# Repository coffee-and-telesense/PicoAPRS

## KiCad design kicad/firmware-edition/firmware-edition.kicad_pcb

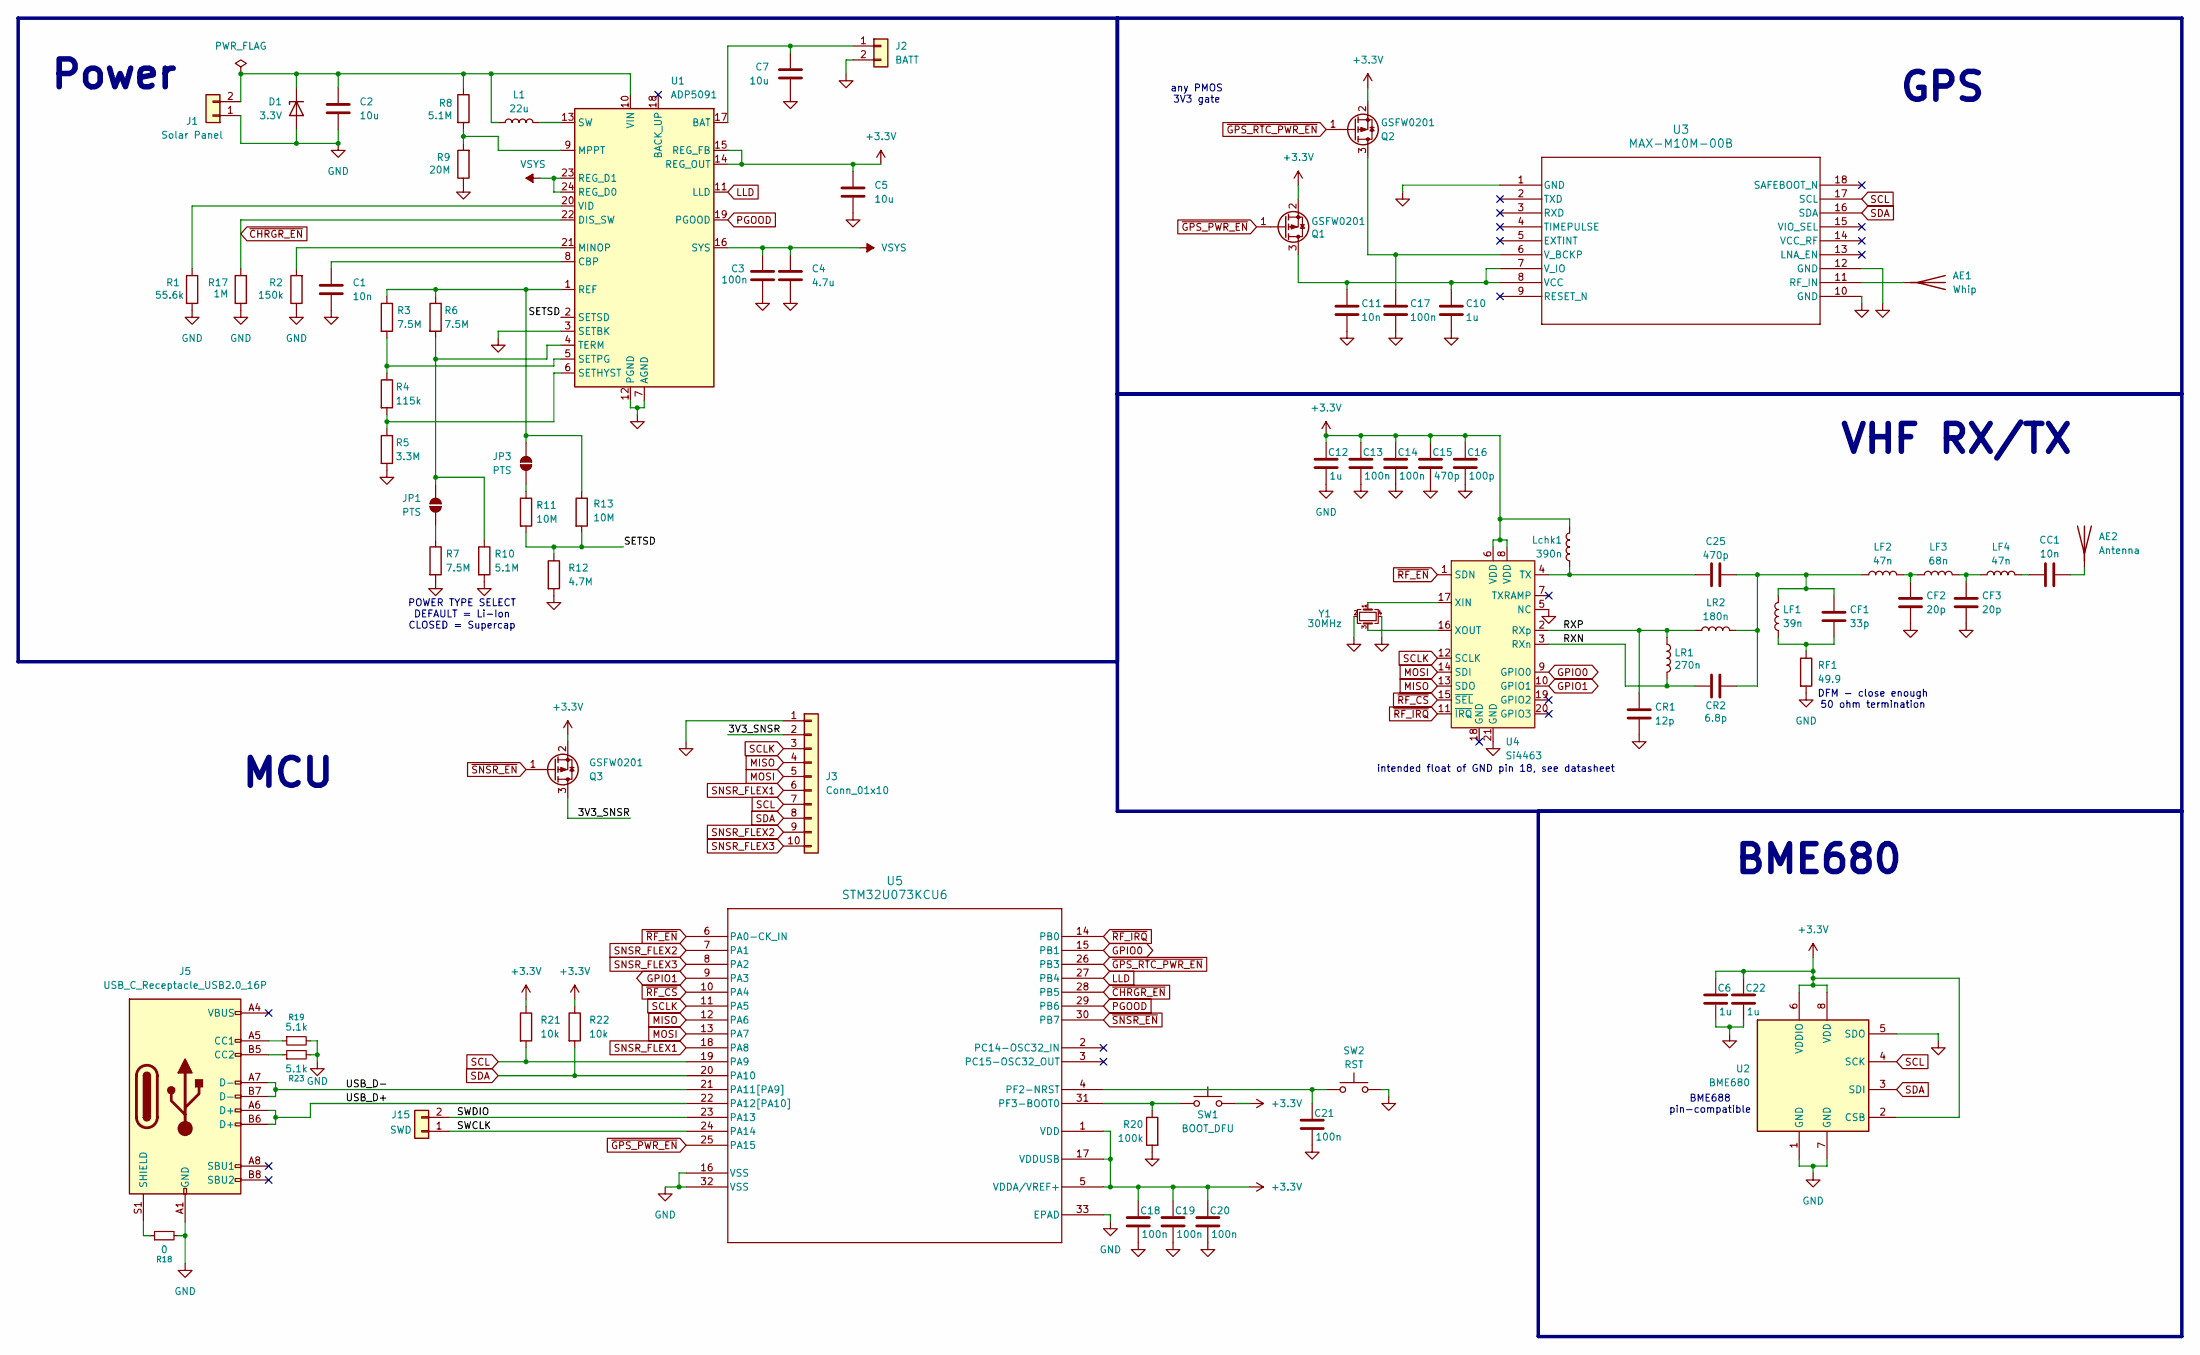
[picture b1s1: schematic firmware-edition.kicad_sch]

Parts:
AE1: Whip; SolderWirePad_1x01_SMD_1x2mm
AE2: Antenna; SolderWirePad_1x01_SMD_1x2mm
C1, C11: 10n; C_0402_1005Metric
C2, C5, C7: 10u; C_0402_1005Metric
C3, C13, C14, C17, C18, C19, C20, C21: 100n; C_0402_1005Metric
C4: 4.7u; C_0402_1005Metric
C6, C10, C12, C22: 1u; C_0402_1005Metric
C15, C25: 470p; C_0402_1005Metric
C16: 100p; C_0402_1005Metric
CC1: 10n; C_0402_1005Metric
CF1: 33p; C_0402_1005Metric
CF2, CF3: 20p; C_0402_1005Metric
CR1: 12p; C_0402_1005Metric
CR2: 6.8p; C_0402_1005Metric
D1: 3.3V; D_0402_1005Metric_Pad0.77x0.64mm_HandSolder
J1: Solar Panel; C_Disc_D3.0mm_W1.6mm_P2.50mm
J2: BATT; C_Disc_D3.0mm_W1.6mm_P2.50mm
J3: Conn_01x10; CON_513389873
J5: USB_C_Receptacle_USB2.0_16P; USB_C_Receptacle_Palconn_UTC16-G
J15: SWD; PinHeader_1x02_P2.54mm_Vertical
JP1, JP3: PTS; SolderJumper-2_P1.3mm_Open_TrianglePad1.0x1.5mm
L1: 22u; L_Vishay_IFSC-1515AH_4x4x1.8mm
LF1: 39n; L_0402_1005Metric
LF2, LF4: 47n; L_0402_1005Metric
LF3: 68n; L_0402_1005Metric
LR1: 270n; L_0402_1005Metric
LR2: 180n; L_0402_1005Metric
Lchk1: 390n; L_0402_1005Metric
Q1, Q2, Q3: GSFW0201; SOT-883
R1: 55.6k; R_0402_1005Metric
R2: 150k; R_0402_1005Metric
R3, R6, R7: 7.5M; R_0402_1005Metric
R4: 115k; R_0402_1005Metric
R5: 3.3M; R_0402_1005Metric
R8, R10: 5.1M; R_0402_1005Metric
R9: 20M; R_0402_1005Metric
R11, R13: 10M; R_0402_1005Metric
R12: 4.7M; R_0402_1005Metric
R17: 1M; R_0402_1005Metric
R18: 0; R_0402_1005Metric
R19, R23: 5.1k; R_0402_1005Metric
R20: 100k; R_0402_1005Metric
R21, R22: 10k; R_0402_1005Metric
RF1: 49.9; R_0402_1005Metric
SW1: BOOT_DFU; SW_Push_1TS009xxxx-xxxx-xxxx_6x6x5mm
SW2: RST; SW_Push_1TS009xxxx-xxxx-xxxx_6x6x5mm
U1: ADP5091; LFCSP-24-1EP_4x4mm_P0.5mm_EP2.3x2.3mm
U2: BME680; Bosch_LGA-8_3x3mm_P0.8mm_ClockwisePinNumbering
U3: MAX-M10M-00B; MOD18_MAX-M10M_UBL
U4: Si4463; QFN-20-1EP_4x4mm_P0.5mm_EP2.6x2.6mm
U5: STM32U073KCU6; UFQFPN-32_STM
Y1: 30MHz; Crystal_SMD_2520-4Pin_2.5x2.0mm

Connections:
+3.3V: C5.1, C6.1, C12.1, C13.1, C14.1, C15.1, C16.1, C18.1, C19.1, C20.1, C22.1, Lchk1.1, Q1.2 (S), Q2.2 (S), Q3.2 (S), R21.1, R22.1, SW1.2, U1.14 (REG_OUT), U1.15 (REG_FB), U2.2 (CSB), U2.6 (VDDIO), U2.8 (VDD), U4.6 (VDD), U4.8 (VDD), U5.1 (VDD), U5.5 (VDDA/VREF+), U5.17 (VDDUSB)
/3V3_SNSR: J3.2, Q3.3 (D)
/RXN: CR2.1, LR1.1, U4.3 (RXn)
/RXP: CR1.1, LR1.2, LR2.1, U4.2 (RXp)
/SETSD: R11.2, R12.1, R13.2, U1.2 (SETSD)
/SWCLK: J15.1, U5.24 (PA14)
/SWDIO: J15.2, U5.23 (PA13)
/USB_D+: J5.A6 (D+), J5.B6 (D+), U5.22 (PA12[PA10])
/USB_D-: J5.A7 (D-), J5.B7 (D-), U5.21 (PA11[PA9])
GND: C1.2, C2.2, C3.2, C4.2, C5.2, C6.2, C7.2, C10.2, C11.2, C12.2, C13.2, C14.2, C15.2, C16.2, C17.2, C18.2, C19.2, C20.2, C21.2, C22.2, CF2.2, CF3.2, CR1.2, D1.2 (A), J1.1, J2.2, J3.1, J5.A1 (GND), J5.A12 (GND), J5.B1 (GND), J5.B12 (GND), R1.2, R2.1, R5.2, R7.2, R9.1, R10.2, R12.2, R17.1, R18.2, R19.2, R20.2, R23.2, RF1.2, SW2.2, U1.3 (SETBK), U1.7 (AGND), U1.12 (PGND), U1.25 (AGND), U2.1 (GND), U2.5 (SDO), U2.7 (GND), U3.1 (GND), U3.10 (GND), U3.12 (GND), U4.5 (NC), U4.21 (GND), U5.16 (VSS), U5.32 (VSS), U5.33 (EPAD), Y1.2, Y1.4
GPIO0: U4.9 (GPIO0), U5.15 (PB1)
GPIO1: U4.10 (GPIO1), U5.9 (PA3)
LLD: U1.11 (LLD), U5.27 (PB4)
MISO: J3.4, U4.13 (SDO), U5.12 (PA6)
MOSI: J3.5, U4.14 (SDI), U5.13 (PA7)
unnamed: AE1.1 (A), U3.11 (RF_IN)
unnamed: AE2.1 (A), CC1.2
unnamed: C25.2, CF1.1, CR2.2, LF1.2, LF2.1, LR2.2
unnamed: CC1.1, LF4.2
unnamed: CF1.2, LF1.1, RF1.1
unnamed: CF2.1, LF2.2, LF3.1
unnamed: CF3.1, LF3.2, LF4.1
unnamed: C2.1, D1.1 (K), J1.2, L1.1, R8.1, U1.10 (VIN)
unnamed: C7.1, J2.1, U1.17 (BAT)
unnamed: J5.A5 (CC1), R19.1
unnamed: J5.B5 (CC2), R23.1
unnamed: J5.S1 (SHIELD), R18.1
unnamed: JP1.1 (A), R7.1
unnamed: JP1.2 (B), R6.2, R10.1, U1.4 (TERM)
unnamed: JP3.1 (A), R11.1
unnamed: JP3.2 (B), R3.1, R6.1, R13.1, U1.1 (REF)
unnamed: C10.1, C11.1, Q1.3 (D), U3.7 (V_IO), U3.8 (VCC)
unnamed: C17.1, Q2.3 (D), U3.6 (V_BCKP)
unnamed: C1.1, U1.8 (CBP)
unnamed: R2.2, U1.21 (MINOP)
unnamed: R8.2, R9.2, U1.9 (MPPT)
unnamed: R4.2, R5.1, U1.6 (SETHYST)
unnamed: R3.2, R4.1, U1.5 (SETPG)
unnamed: L1.2, U1.13 (SW)
unnamed: R1.1, U1.20 (VID)
unnamed: C25.1, Lchk1.2, U4.4 (TX)
unnamed: U4.17 (XIN), Y1.1
unnamed: U4.16 (XOUT), Y1.3
unnamed: C21.1, SW2.1, U5.4 (PF2-NRST)
unnamed: R20.1, SW1.1, U5.31 (PF3-BOOT0)
PGOOD: U1.19 (PGOOD), U5.29 (PB6)
SCL: J3.7, R21.2, U2.4 (SCK), U3.17 (SCL), U5.19 (PA9)
SCLK: J3.3, U4.12 (SCLK), U5.11 (PA5)
SDA: J3.8, R22.2, U2.3 (SDI), U3.16 (SDA), U5.20 (PA10)
SNSR_FLEX1: J3.6, U5.18 (PA8)
SNSR_FLEX2: J3.9, U5.7 (PA1)
SNSR_FLEX3: J3.10, U5.8 (PA2)
VSYS: C3.1, C4.1, U1.16 (SYS), U1.23 (REG_D1), U1.24 (REG_D0)
~CHRGR_EN: R17.2, U1.22 (DIS_SW), U5.28 (PB5)
~GPS_PWR_EN: Q1.1 (G), U5.25 (PA15)
~GPS_RTC_PWR_EN: Q2.1 (G), U5.26 (PB3)
~RF_CS: U4.15 (~SEL), U5.10 (PA4)
~RF_EN: U4.1 (SDN), U5.6 (PA0-CK_IN)
~RF_IRQ: U4.11 (~IRQ), U5.14 (PB0)
~SNSR_EN: Q3.1 (G), U5.30 (PB7)

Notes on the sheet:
intended float of GND pin 18, see datasheet
GPS
DFM - close enough 50 ohm termination
Power
MCU
BME688 pin-compatible
VHF RX/TX
BME680
any PMOS 3V3 gate
POWER TYPE SELECT DEFAULT = Li-Ion CLOSED = Supercap

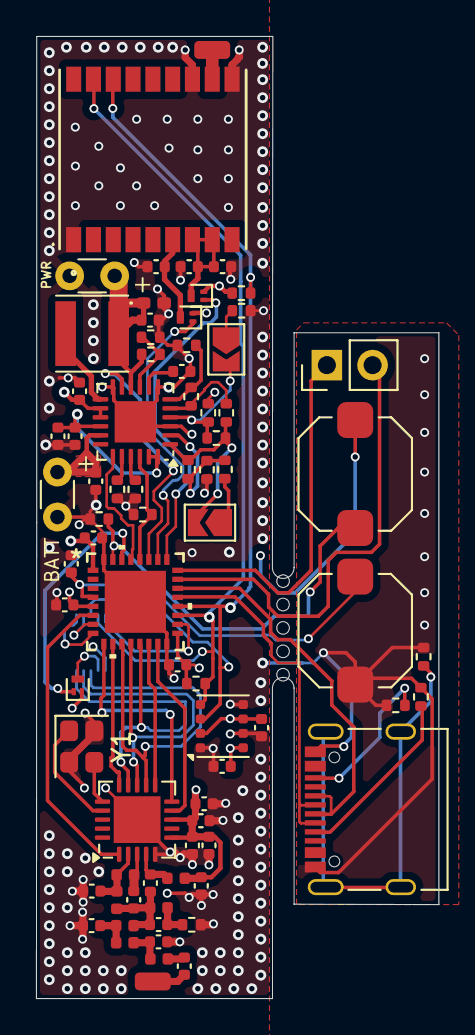
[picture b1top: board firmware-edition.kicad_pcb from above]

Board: 4 copper layers, 22.4 x 53.4 mm, 77 parts (1 on the bottom side), 60 nets.

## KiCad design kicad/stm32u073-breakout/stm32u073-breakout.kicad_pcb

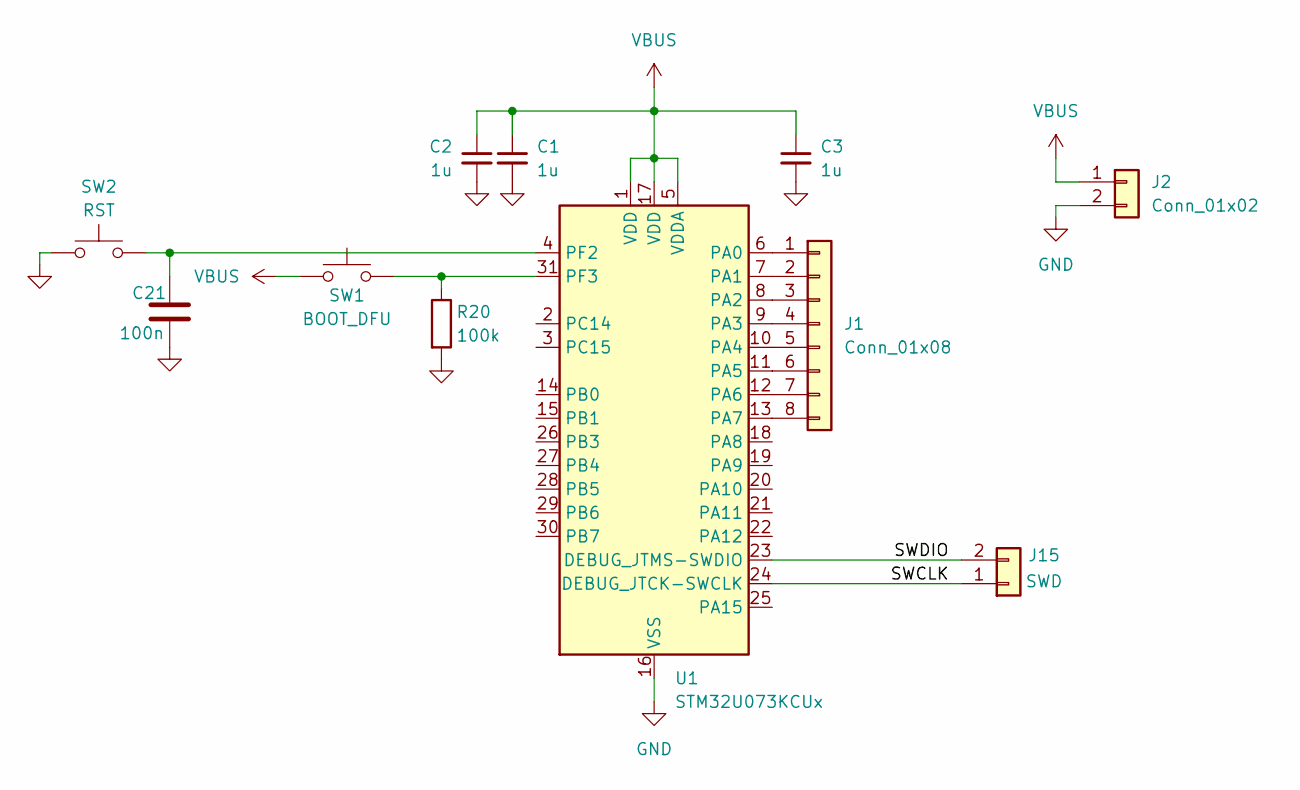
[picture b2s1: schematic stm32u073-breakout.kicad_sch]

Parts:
C1, C2, C3: 1u; C_0603_1608Metric
C21: 100n; C_0603_1608Metric
J1: Conn_01x08; PinHeader_1x08_P2.54mm_Vertical
J2: Conn_01x02; PinHeader_1x02_P2.54mm_Vertical
J15: SWD; PinHeader_1x02_P2.54mm_Vertical
R20: 100k; R_0603_1608Metric
SW1: BOOT_DFU; SW_SPST_B3S-1000
SW2: RST; SW_SPST_B3S-1000
U1: STM32U073KCUx; QFN-32-1EP_5x5mm_P0.5mm_EP3.45x3.45mm

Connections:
/SWCLK: J15.1, U1.24 (DEBUG_JTCK-SWCLK)
/SWDIO: J15.2, U1.23 (DEBUG_JTMS-SWDIO)
GND: C1.2, C2.2, C3.2, C21.2, J2.2, R20.2, SW2.2, U1.16 (VSS), U1.32 (VSS), U1.33 (VSS)
unnamed: J1.1, U1.6 (PA0)
unnamed: J1.2, U1.7 (PA1)
unnamed: J1.3, U1.8 (PA2)
unnamed: J1.4, U1.9 (PA3)
unnamed: J1.5, U1.10 (PA4)
unnamed: J1.6, U1.11 (PA5)
unnamed: J1.7, U1.12 (PA6)
unnamed: J1.8, U1.13 (PA7)
unnamed: C21.1, SW2.1, U1.4 (PF2)
unnamed: R20.1, SW1.1, U1.31 (PF3)
VBUS: C1.1, C2.1, C3.1, J2.1, SW1.2, U1.1 (VDD), U1.5 (VDDA), U1.17 (VDD)

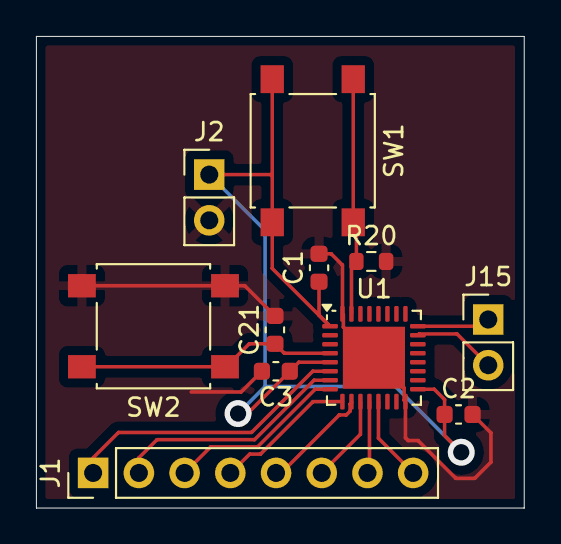
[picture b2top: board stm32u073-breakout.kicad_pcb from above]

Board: 2 copper layers, 27.1 x 26.2 mm, 11 parts (0 on the bottom side), 14 nets.

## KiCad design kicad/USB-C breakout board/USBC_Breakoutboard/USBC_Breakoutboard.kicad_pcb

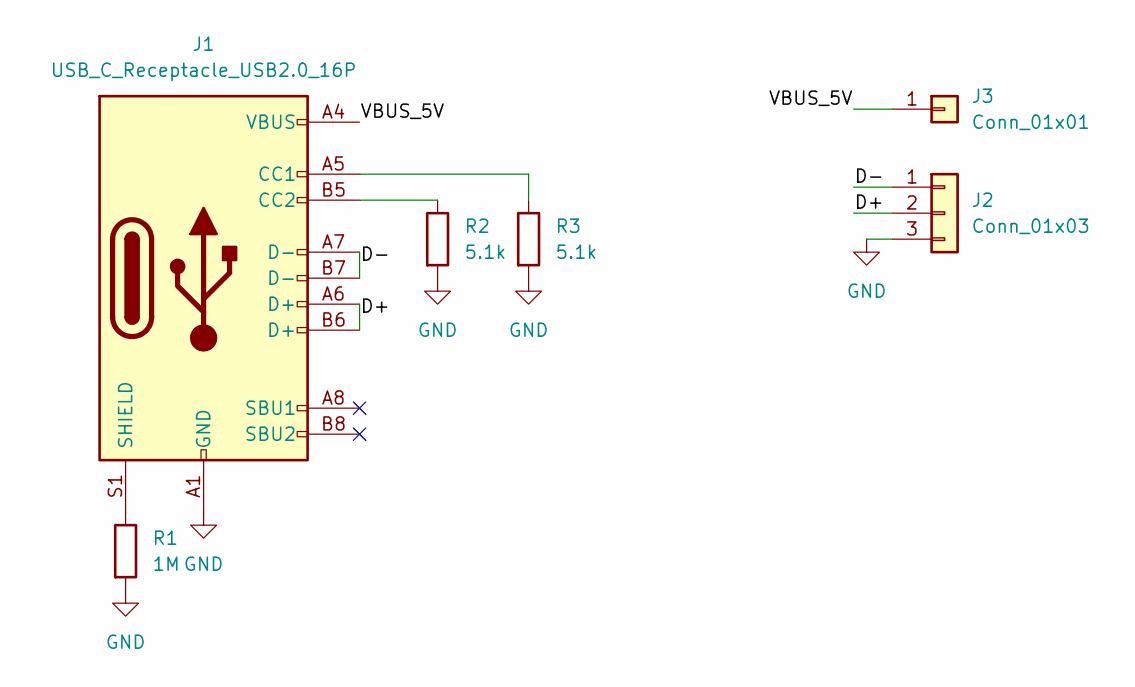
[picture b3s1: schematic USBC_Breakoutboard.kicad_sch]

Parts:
J1: USB_C_Receptacle_USB2.0_16P; USB_C_Receptacle_GCT_USB4105-xx-A_16P_TopMnt_Horizontal
J2: Conn_01x03; PinHeader_1x03_P2.54mm_Vertical
J3: Conn_01x01; PinHeader_1x01_P2.54mm_Vertical
R1: 1M; R_0603_1608Metric
R2, R3: 5.1k; R_0603_1608Metric

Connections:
/D+: J1.A6 (D+), J1.B6 (D+), J2.2
/D-: J1.A7 (D-), J1.B7 (D-), J2.1
/VBUS_5V: J1.A4 (VBUS), J1.A9 (VBUS), J1.B4 (VBUS), J1.B9 (VBUS), J3.1
GND: J1.A1 (GND), J1.A12 (GND), J1.B1 (GND), J1.B12 (GND), J2.3, R1.2, R2.2, R3.2
unnamed: J1.A5 (CC1), R3.1
unnamed: J1.B5 (CC2), R2.1
unnamed: J1.S1 (SHIELD), R1.1

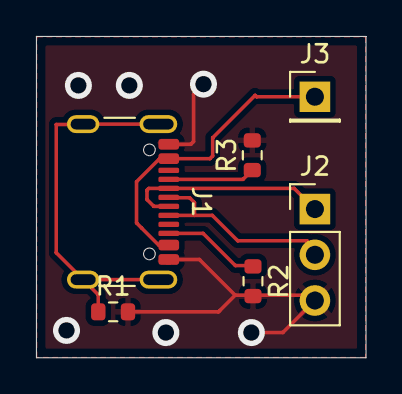
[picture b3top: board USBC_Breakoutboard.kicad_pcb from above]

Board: 2 copper layers, 18.3 x 17.9 mm, 6 parts (0 on the bottom side), 7 nets.

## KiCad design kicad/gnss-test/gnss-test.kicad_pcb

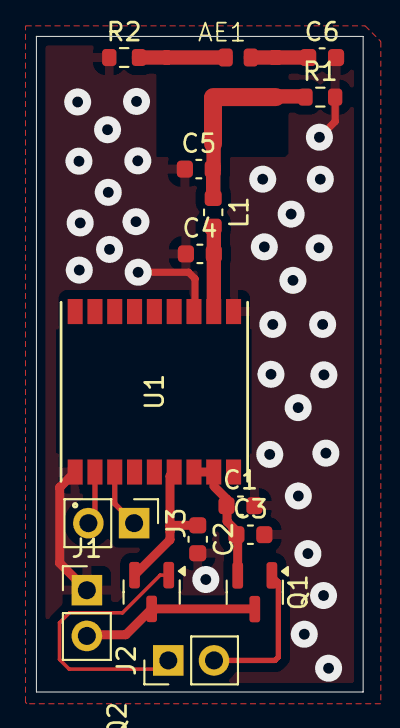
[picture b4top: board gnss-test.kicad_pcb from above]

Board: 2 copper layers, 18.2 x 36.4 mm, 16 parts (0 on the bottom side), 11 nets.

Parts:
AE1: Antenna; AC30157-01 GNSS Ceramic Chip
C1: 10n; C_0603_1608Metric
C2: 100n; C_0603_1608Metric
C3: 1u; C_0603_1608Metric
C4, C5: DNP; C_0603_1608Metric
C6: 10p; C_0603_1608Metric
J1: PWR; PinHeader_1x02_P2.54mm_Vertical
J2: EN; PinHeader_1x02_P2.54mm_Vertical
J3: UART; PinHeader_1x02_P2.54mm_Vertical
L1: 2.0n; L_0603_1608Metric
Q1, Q2: BSS84; SOT-23
R1, R2: 0; R_0603_1608Metric
U1: MAX-M10M-00B; MOD18_MAX-M10M_UBL

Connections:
+3.3V: J1.2, Q1.3 (D), Q2.3 (D)
GND: C1.2, C2.2, C3.2, C4.1, C5.1, C6.2, J1.1, R1.2, R2.1, U1.1 (GND), U1.10 (GND), U1.12 (GND)
GPS_UART_RX: J3.2, U1.2 (TXD)
GPS_UART_TX: J3.1, U1.3 (RXD)
unnamed: C6.1, R2.2
unnamed: C5.2, L1.1, R1.1
unnamed: C1.1, C3.1, Q1.2 (S), U1.7 (V_IO), U1.8 (VCC)
unnamed: C2.1, Q2.2 (S), U1.6 (V_BCKP)
unnamed: C4.2, L1.2, U1.11 (RF_IN)
~GPS_PWR_EN: J2.2, Q1.1 (G)
~GPS_RTC_PWR_EN: J2.1, Q2.1 (G)

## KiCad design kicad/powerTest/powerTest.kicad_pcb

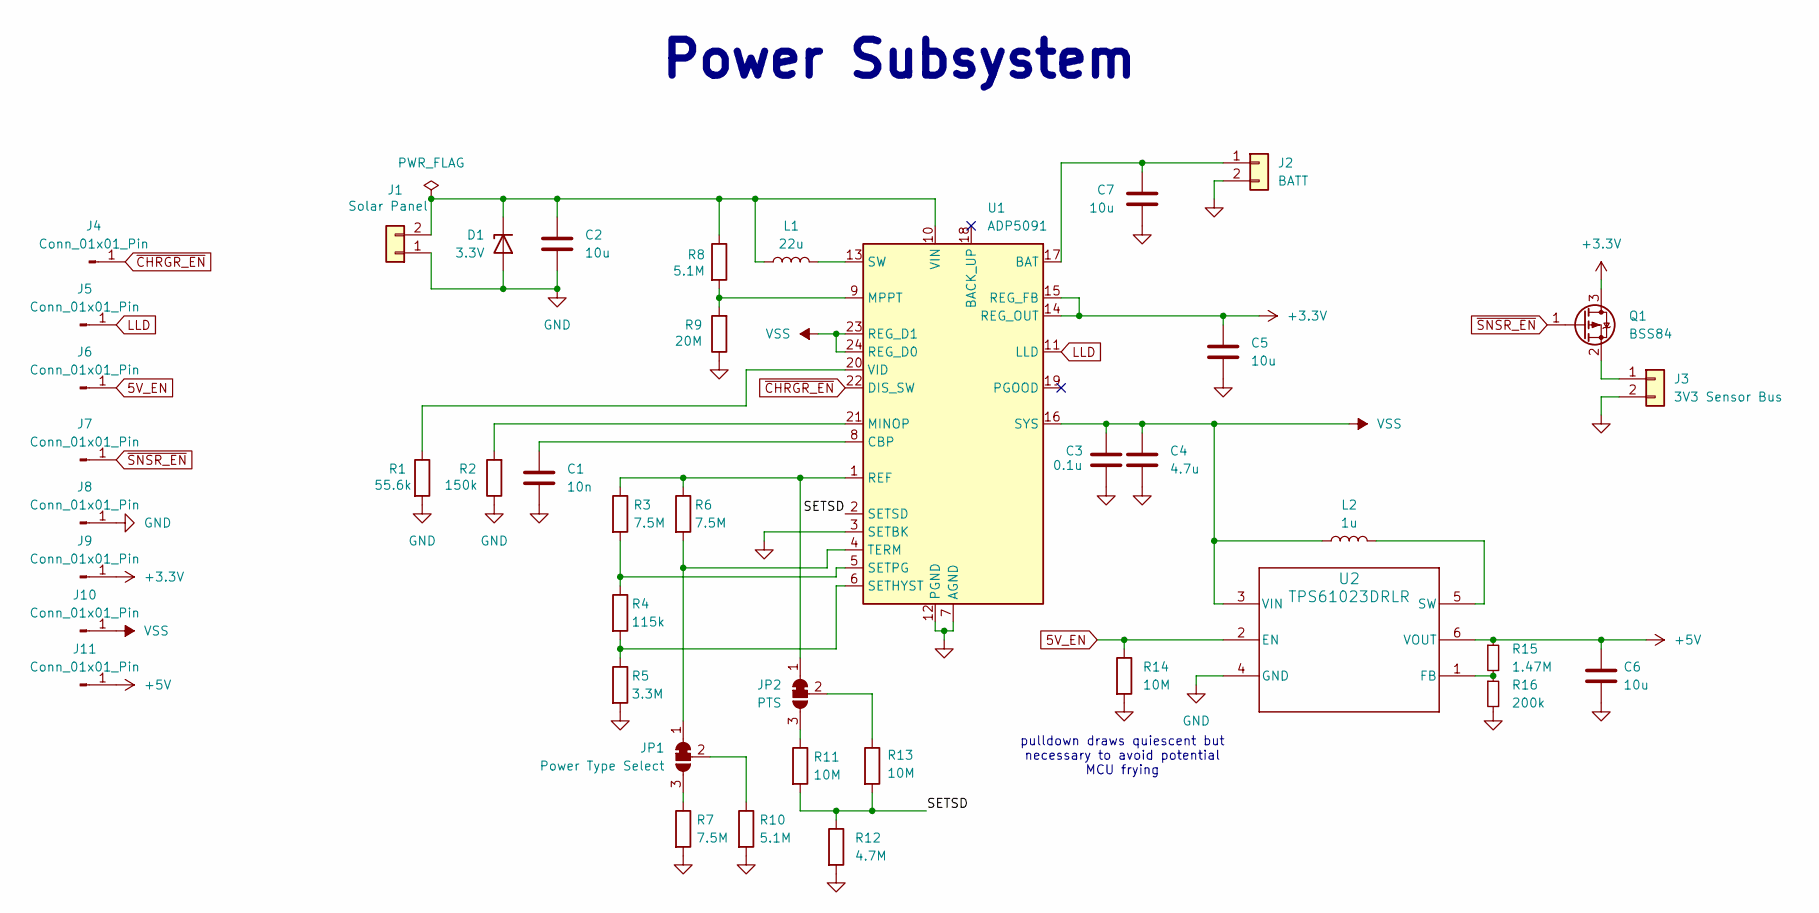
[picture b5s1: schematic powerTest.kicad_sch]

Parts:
C1: 10n; C_0603_1608Metric
C2, C5, C6, C7: 10u; C_0603_1608Metric
C3: 0.1u; C_0603_1608Metric
C4: 4.7u; C_0603_1608Metric
D1: 3.3V; D_0402_1005Metric_Pad0.77x0.64mm_HandSolder
J1: Solar Panel; PinSocket_1x02_P2.54mm_Vertical
J2: BATT; PinSocket_1x02_P2.54mm_Vertical
J3: 3V3 Sensor Bus; PinSocket_1x02_P2.54mm_Vertical
J4, J5, J6, J7, J8, J9, J10, J11: Conn_01x01_Pin; PinHeader_1x01_P2.54mm_Vertical
JP1: Power Type Select; SolderJumper-3_P1.3mm_Bridged12_Pad1.0x1.5mm
JP2: PTS; SolderJumper-3_P1.3mm_Bridged12_Pad1.0x1.5mm
L1: 22u; L_Vishay_IFSC-1515AH_4x4x1.8mm
L2: 1u; L_0603_1608Metric
Q1: BSS84; SOT-23
R1: 55.6k; R_0603_1608Metric
R2: 150k; R_0603_1608Metric
R3, R6, R7: 7.5M; R_0603_1608Metric
R4: 115k; R_0603_1608Metric
R5: 3.3M; R_0603_1608Metric
R8, R10: 5.1M; R_0603_1608Metric
R9: 20M; R_0603_1608Metric
R11, R13, R14: 10M; R_0603_1608Metric
R12: 4.7M; R_0603_1608Metric
R15: 1.47M; R_0603_1608Metric
R16: 200k; R_0603_1608Metric
U1: ADP5091; LFCSP-24-1EP_4x4mm_P0.5mm_EP2.3x2.3mm
U2: TPS61023DRLR; DRL0006A

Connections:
5V_EN: J6.1, R14.1, U2.2 (EN)
+3.3V: C5.1, J9.1, Q1.3 (D), U1.14 (REG_OUT), U1.15 (REG_FB)
+5V: C6.1, J11.1, R15.1, U2.6 (VOUT)
/SETSD: R11.2, R12.1, R13.2, U1.2 (SETSD)
GND: C1.2, C2.2, C3.2, C4.2, C5.2, C6.2, C7.2, D1.2 (A), J1.1, J2.2, J3.2, J8.1, R1.2, R2.1, R5.2, R7.2, R9.1, R10.2, R12.2, R14.2, R16.2, U1.3 (SETBK), U1.7 (AGND), U1.12 (PGND), U1.25 (AGND), U2.4 (GND)
LLD: J5.1, U1.11 (LLD)
unnamed: C2.1, D1.1 (K), J1.2, L1.1, R8.1, U1.10 (VIN)
unnamed: C7.1, J2.1, U1.17 (BAT)
unnamed: J3.1, Q1.2 (S)
unnamed: JP1.1 (A), R6.2, U1.4 (TERM)
unnamed: JP1.3 (B), R7.1
unnamed: JP1.2 (C), R10.1
unnamed: JP2.1 (A), R3.1, R6.1, U1.1 (REF)
unnamed: JP2.3 (B), R11.1
unnamed: JP2.2 (C), R13.1
unnamed: C1.1, U1.8 (CBP)
unnamed: R2.2, U1.21 (MINOP)
unnamed: R8.2, R9.2, U1.9 (MPPT)
unnamed: R4.2, R5.1, U1.6 (SETHYST)
unnamed: R3.2, R4.1, U1.5 (SETPG)
unnamed: L1.2, U1.13 (SW)
unnamed: R1.1, U1.20 (VID)
unnamed: R15.2, R16.1, U2.1 (FB)
unnamed: L2.2, U2.5 (SW)
VSS: C3.1, C4.1, J10.1, L2.1, U1.16 (SYS), U1.23 (REG_D1), U1.24 (REG_D0), U2.3 (VIN)
~CHRGR_EN: J4.1, U1.22 (DIS_SW)
~SNSR_EN: J7.1, Q1.1 (G)

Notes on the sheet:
pulldown draws quiescent but necessary to avoid potential MCU frying
Power Subsystem

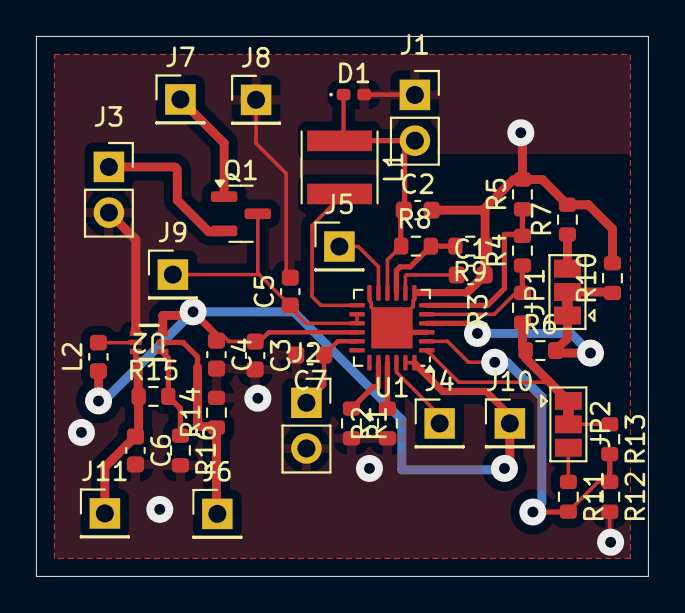
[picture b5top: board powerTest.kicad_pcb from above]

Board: 2 copper layers, 34.0 x 30.0 mm, 42 parts (0 on the bottom side), 27 nets.

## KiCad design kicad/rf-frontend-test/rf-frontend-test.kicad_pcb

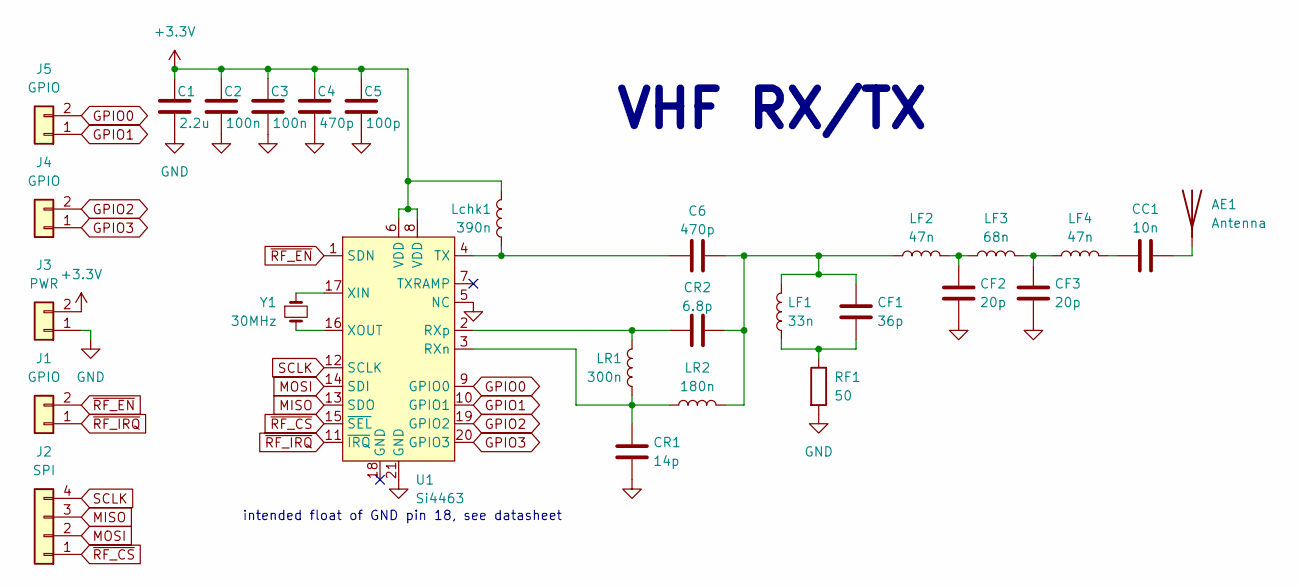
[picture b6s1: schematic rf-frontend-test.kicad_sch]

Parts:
AE1: Antenna; SolderWirePad_1x01_SMD_1x2mm
C1: 2.2u; C_0402_1005Metric
C2, C3: 100n; C_0402_1005Metric
C4, C6: 470p; C_0402_1005Metric
C5: 100p; C_0402_1005Metric
CC1: 10n; C_0402_1005Metric
CF1: 36p; C_0402_1005Metric
CF2, CF3: 20p; C_0402_1005Metric
CR1: 14p; C_0402_1005Metric
CR2: 6.8p; C_0402_1005Metric
J1, J4, J5: GPIO; PinHeader_1x02_P2.54mm_Vertical
J2: SPI; PinHeader_1x04_P2.54mm_Vertical
J3: PWR; PinHeader_1x02_P2.54mm_Vertical
LF1: 33n; L_0402_1005Metric
LF2, LF4: 47n; L_0402_1005Metric
LF3: 68n; L_0402_1005Metric
LR1: 300n; L_0402_1005Metric
LR2: 180n; L_0402_1005Metric
Lchk1: 390n; L_0402_1005Metric
RF1: 50; R_0402_1005Metric
U1: Si4463; QFN-20-1EP_4x4mm_P0.5mm_EP2.6x2.6mm
Y1: 30MHz; Crystal_SMD_Abracon_ABM3-2Pin_5.0x3.2mm

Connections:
+3.3V: C1.1, C2.1, C3.1, C4.1, C5.1, J3.2, Lchk1.1, U1.6 (VDD), U1.8 (VDD)
GND: C1.2, C2.2, C3.2, C4.2, C5.2, CF2.2, CF3.2, CR1.2, J3.1, RF1.2, U1.5 (NC), U1.21 (GND)
GPIO0: J5.2, U1.9 (GPIO0)
GPIO1: J5.1, U1.10 (GPIO1)
GPIO2: J4.2, U1.19 (GPIO2)
GPIO3: J4.1, U1.20 (GPIO3)
MISO: J2.3, U1.13 (SDO)
MOSI: J2.2, U1.14 (SDI)
unnamed: AE1.1 (A), CC1.2
unnamed: C6.2, CF1.1, CR2.2, LF1.2, LF2.1, LR2.2
unnamed: CC1.1, LF4.2
unnamed: CF1.2, LF1.1, RF1.1
unnamed: CF2.1, LF2.2, LF3.1
unnamed: CF3.1, LF3.2, LF4.1
unnamed: CR1.1, LR1.2, LR2.1, U1.3 (RXn)
unnamed: CR2.1, LR1.1, U1.2 (RXp)
unnamed: C6.1, Lchk1.2, U1.4 (TX)
unnamed: U1.17 (XIN), Y1.1
unnamed: U1.16 (XOUT), Y1.2
SCLK: J2.4, U1.12 (SCLK)
~RF_CS: J2.1, U1.15 (~SEL)
~RF_EN: J1.2, U1.1 (SDN)
~RF_IRQ: J1.1, U1.11 (~IRQ)

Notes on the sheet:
intended float of GND pin 18, see datasheet
VHF RX/TX

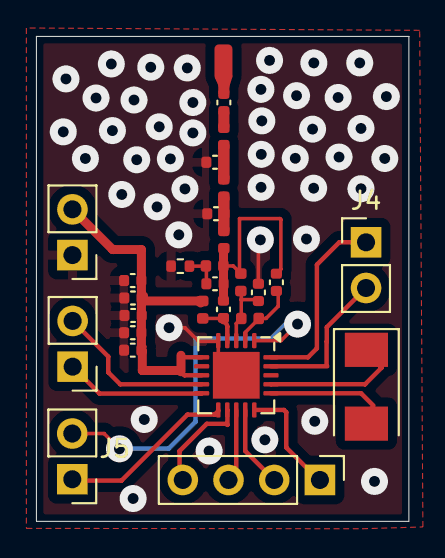
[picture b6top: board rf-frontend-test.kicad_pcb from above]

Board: 2 copper layers, 20.7 x 26.9 mm, 28 parts (0 on the bottom side), 23 nets.

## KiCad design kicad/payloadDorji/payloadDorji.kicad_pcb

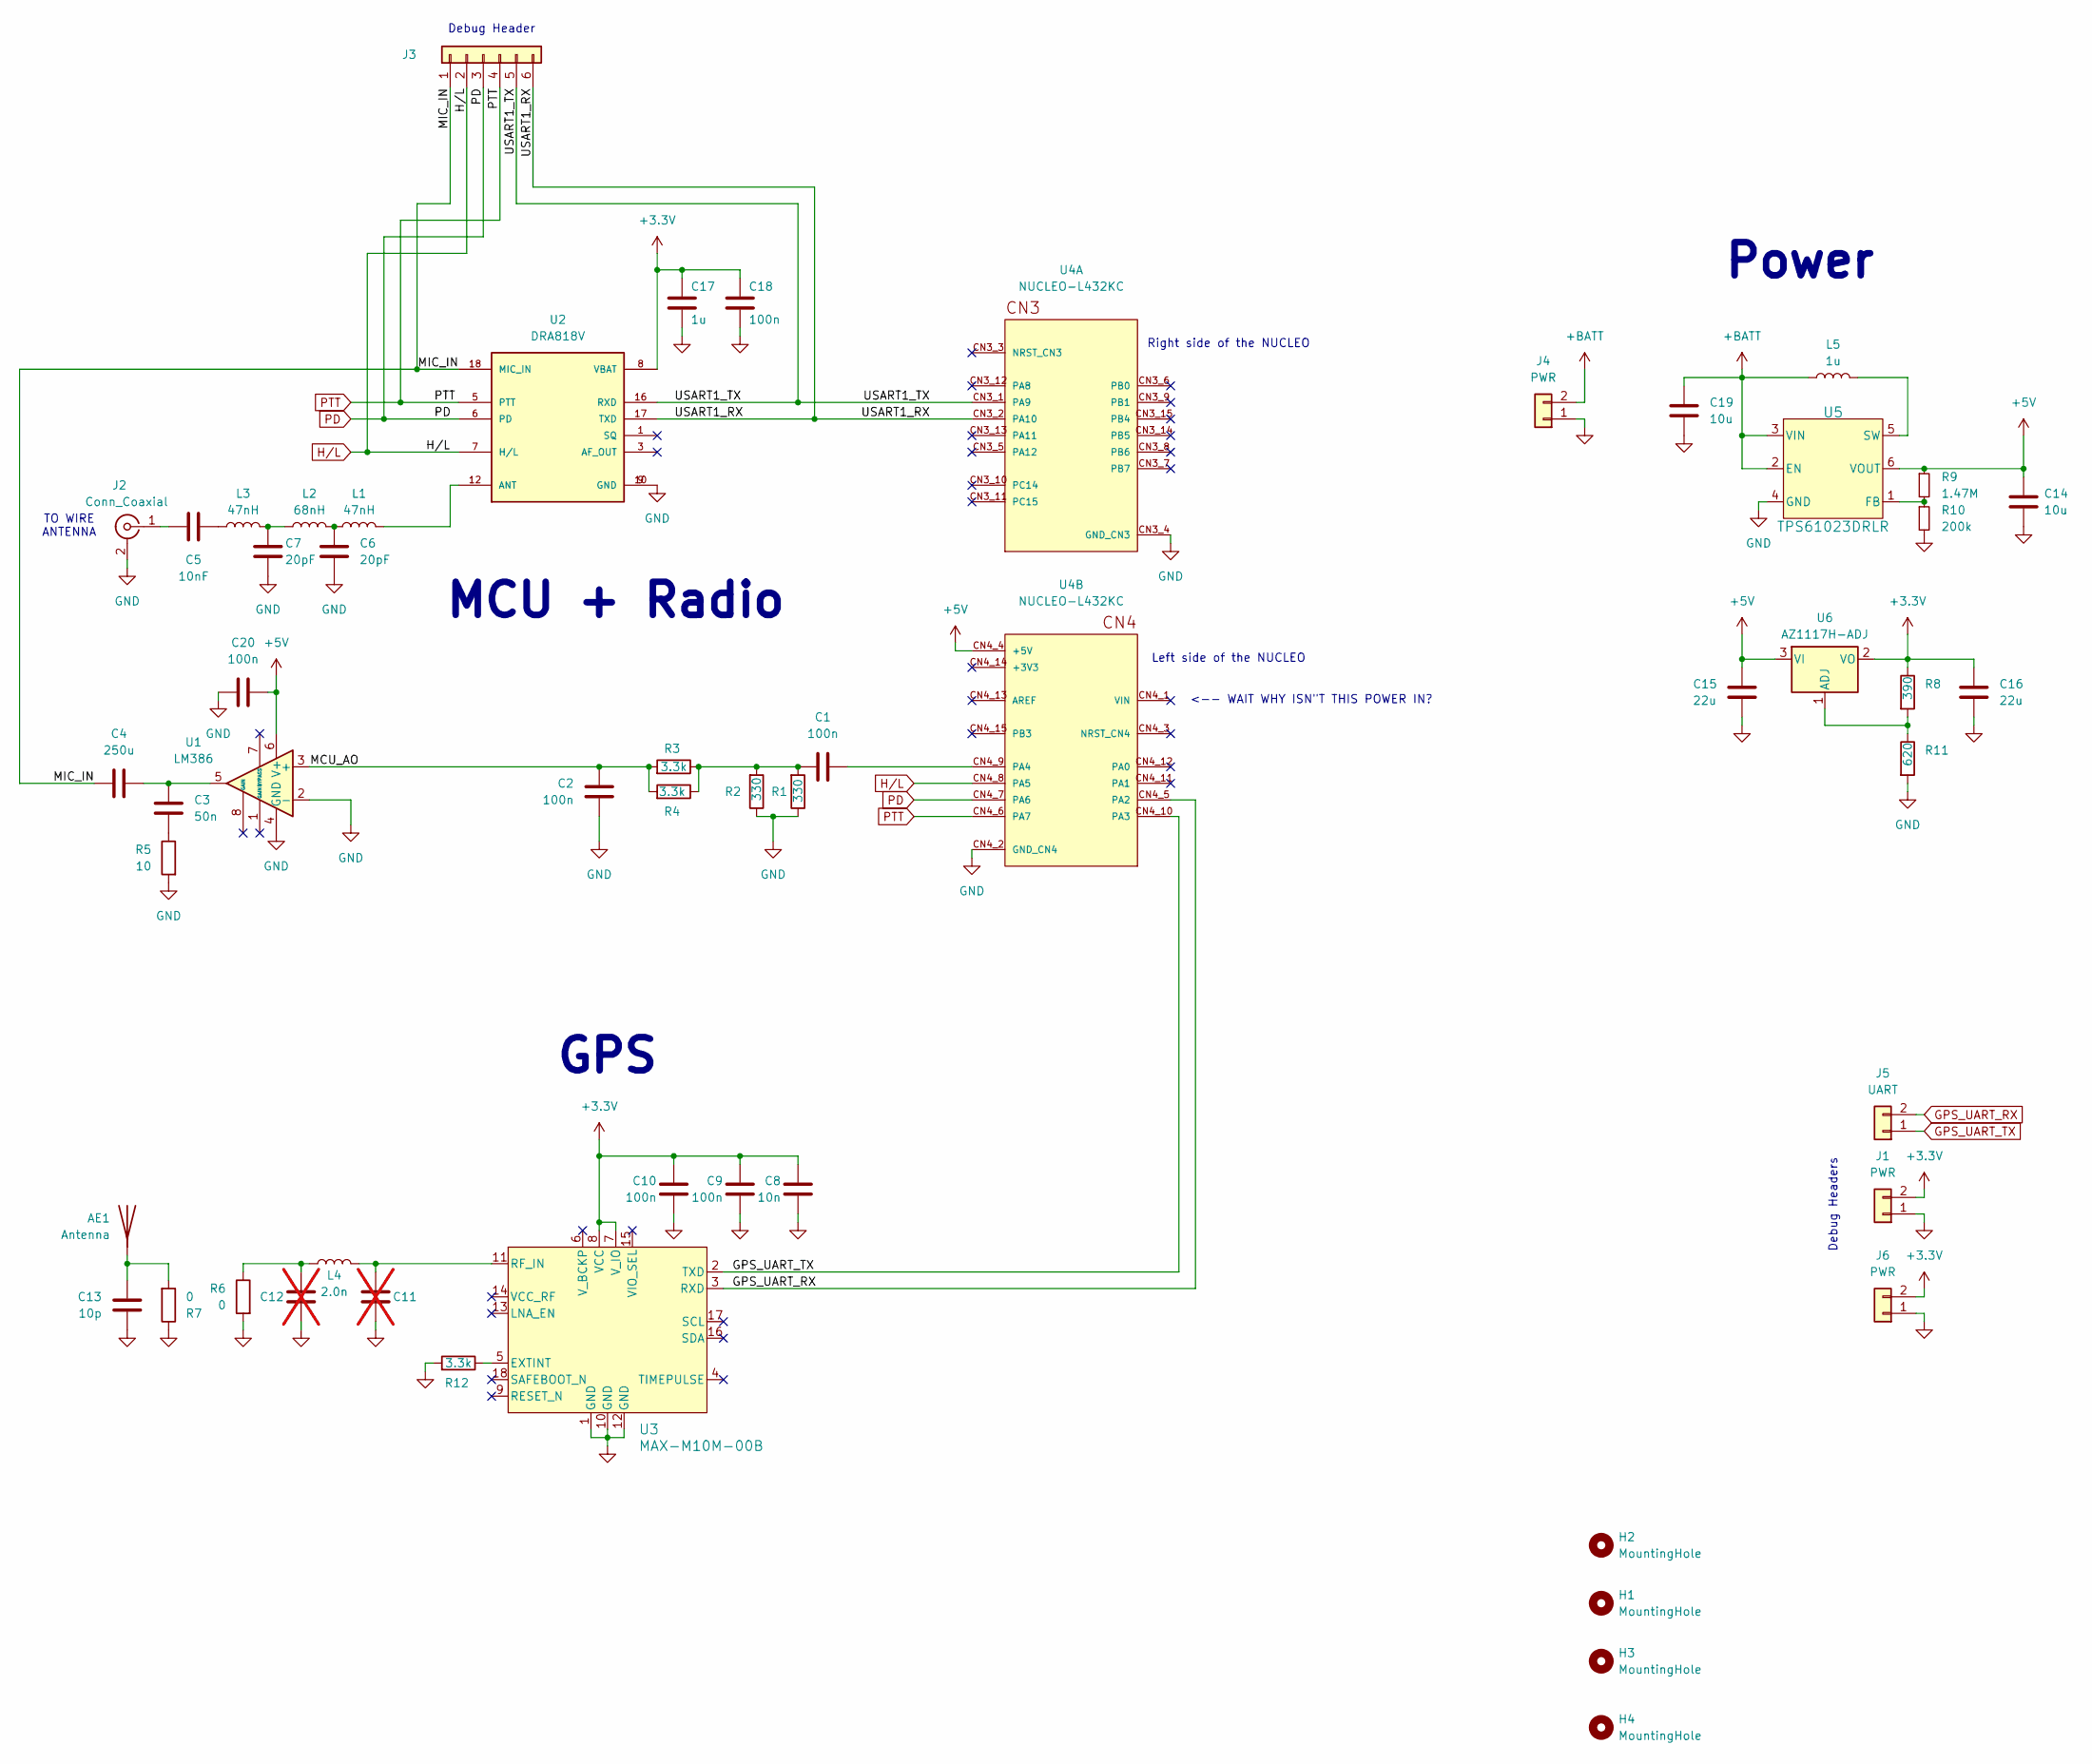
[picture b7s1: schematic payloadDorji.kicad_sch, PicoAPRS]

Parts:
AE1: Antenna; AC30157-01 GNSS Ceramic Chip
C1, C2, C9, C10, C18, C20: 100n; C_0603_1608Metric
C3: 50n; C_0603_1608Metric
C4: 250u; C_1210_3225Metric
C5: 10nF; C_0603_1608Metric
C6, C7: 20pF; C_0603_1608Metric
C8: 10n; C_0603_1608Metric
C11, C12: C_0603_1608Metric; not fitted
C13: 10p; C_0603_1608Metric
C14, C19: 10u; C_0603_1608Metric
C15, C16: 22u; C_0603_1608Metric
C17: 1u; C_0603_1608Metric
H1, H2, H3, H4: MountingHole; MountingHole_4.3mm_M4
J1, J4, J6: PWR; PinHeader_1x02_P2.54mm_Vertical
J2: Conn_Coaxial; SMA_Molex_73251-1153_EdgeMount_Horizontal
J3: Conn_01x06_Male; PinHeader_1x06_P2.54mm_Vertical
J5: UART; PinHeader_1x02_P2.54mm_Vertical
L1, L3: 47nH; L_0603_1608Metric
L2: 68nH; L_0603_1608Metric
L4: 2.0n; L_0603_1608Metric
L5: 1u; L_1008_2520Metric
R1, R2: 330; R_0603_1608Metric
R3, R4, R12: 3.3k; R_0603_1608Metric
R5: 10; R_0603_1608Metric
R6, R7: 0; R_0603_1608Metric
R8: 390; R_0603_1608Metric
R9: 1.47M; R_0603_1608Metric
R10: 200k; R_0603_1608Metric
R11: 620; R_0603_1608Metric
U1: LM386; DIP-8_W7.62mm_Socket
U2: DRA818V; DORJI_DRA818V; PART_REV 1.23
U3: MAX-M10M-00B; MOD18_MAX-M10M_UBL
U4: NUCLEO-L432KC; MODULE_NUCLEO-L432KC; PARTREV N/A
U5: TPS61023DRLR; DRL0006A
U6: AZ1117H-ADJ; SOT-223-3_TabPin2

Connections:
+3.3V: C8.1, C9.1, C10.1, C16.1, C17.1, C18.1, J1.2, J6.2, R8.1, U2.8 (VBAT), U3.7 (V_IO), U3.8 (VCC), U6.2 (VO)
+5V: C14.1, C15.1, C20.1, R9.1, U1.6 (V+), U4.CN4_4 (+5V), U5.6 (VOUT), U6.3 (VI)
+BATT: C19.1, J4.2, L5.1, U5.2 (EN), U5.3 (VIN)
/MCU_AO: C2.2, R3.2, R4.2, U1.3 (+)
/MIC_IN: C4.2, J3.1, U2.18 (MIC_IN)
/USART1_RX: J3.6, U2.17 (TXD), U4.CN3_2 (PA10)
/USART1_TX: J3.5, U2.16 (RXD), U4.CN3_1 (PA9)
GND: C2.1, C6.2, C7.1, C8.2, C9.2, C10.2, C11.1, C12.1, C13.2, C14.2, C15.2, C16.2, C17.2, C18.2, C19.2, C20.2, J1.1, J2.2 (Ext), J4.1, J6.1, R1.1, R2.1, R5.2, R6.2, R7.1, R10.2, R11.2, R12.2, U1.2 (-), U1.4 (GND), U2.9 (GND), U2.10 (GND), U3.1 (GND), U3.10 (GND), U3.12 (GND), U4.CN3_4 (GND_CN3), U4.CN4_2 (GND_CN4), U5.4 (GND)
GPS_UART_RX: J5.2, U3.3 (RXD), U4.CN4_5 (PA2)
GPS_UART_TX: J5.1, U3.2 (TXD), U4.CN4_10 (PA3)
H/L: J3.2, U2.7 (H/L), U4.CN4_8 (PA5)
unnamed: AE1.1 (A), C13.1, R7.2
unnamed: C1.2, R1.2, R2.2, R3.1, R4.1
unnamed: C3.1, C4.1, U1.5
unnamed: C3.2, R5.1
unnamed: C5.2, L3.1
unnamed: C6.1, L1.1, L2.2
unnamed: C7.2, L2.1, L3.2
unnamed: C12.2, L4.1, R6.1
unnamed: C5.1, J2.1 (In)
unnamed: L1.2, U2.12 (ANT)
unnamed: R12.1, U3.5 (EXTINT)
unnamed: C11.2, L4.2, U3.11 (RF_IN)
unnamed: C1.1, U4.CN4_9 (PA4)
unnamed: R9.2, R10.1, U5.1 (FB)
unnamed: L5.2, U5.5 (SW)
unnamed: R8.2, R11.1, U6.1 (ADJ)
PD: J3.3, U2.6 (PD), U4.CN4_7 (PA6)
PTT: J3.4, U2.5 (PTT), U4.CN4_6 (PA7)

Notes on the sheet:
TO WIRE ANTENNA
GPS
Left side of the NUCLEO
Right side of the NUCLEO
Power
Debug Header
Debug Headers
<-- WAIT WHY ISN"T THIS POWER IN?
MCU + Radio
